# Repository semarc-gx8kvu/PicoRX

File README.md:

SEMARC Version of the PicoRX
============================

As a group we have taken Jon Dawson's design and created:

+ Our own PCB
+ The Box
+ Modifications to the Code

How we modify this fork is up to us as a group. I'm going to suggest that we have a *SEMARC* folder that contains our PCB and Box designs. But we *shouldn't* put code changes in there. I suggest that we put code changes in branches, and then decide as a group whether to include these in the main branch, or maybe even consider submitting pull requests to Jon's original repository.

Pi Pico Rx - A crystal radio for the digital age?
=================================

My first step into the world of electronics was with a crystal radio, just like this one. 

Back then, I don't think it has ever occurred to me that I could make a radio myself, so I wasn't expecting it to work. But when I put the earphone in, I was amazed to hear very faint sounds coming through. I couldn't believe that building a radio could be so simple, and the best part was, it didn't need any batteries! That little experience sparked my interest in electronics.

Times have certainly changed since then, and today, we find ourselves in a golden age for electronics enthusiasts. Back in the ninteen eightees, I could have never imagined that my pocket money would one day buy a device with computing power that could have filled an entire room just a few decades ago.

I often wonder how we can still capture that sense of awe and excitement from my first crystal radio experience. Is it still possible to create something simple yet captivating? 

The Pi Pico Rx - may be the answer to that question. While it may not be quite as straightforward as the crystal radio, the Pi Pico Rx presents a remarkably simple solution. Armed with just a [Raspberry Pi Pico](https://www.raspberrypi.com/products/raspberry-pi-pico/), an analogue switch, and an op-amp, we now have the power to construct a capable SDR receiver covering the LW, MW, and SW bands. With the ability to receive signals from halfway around the globe. I can't help but think that my younger self would have been truly impressed!

Features
--------

+ 0 - 30MHz coverage
+ 250kHz bandwidth SDR reciever
+ CW/SSB/AM/FM reception
+ OLED display
+ simple spectrum scope
+ Headphones/Speaker
+ 500 general purpose memories
+ runs on 3 AAA batteries
+ less than 50mA current consumption

Development
-----------

Pi Pico Rx is currently at the experimental prototyping stage, but it does work. [Read the Docs](https://101-things.readthedocs.io/en/latest/radio_receiver.html) for more technical details!

Getting the Code
----------------

You can find a precompiled binary for PiPicoRx [here](https://github.com/dawsonjon/PicoRX/releases). If you want to build from the C++ source files, follow these instructions.

```
  sudo apt install git
  git clone https://github.com/dawsonjon/PicoRX.git
  cd PicoRX
  git submodule init
  git submodule update
```

User Manual
-----------

You can find the user manual for the PiPicoRx [here](https://github.com/dawsonjon/PicoRX/raw/master/user_manual/Pi%20Pico%20Rx%20User%20Manual.pdf).

Install Pi Pico SDK
-------------------

Follow the [Getting started with the Raspberry Pi Pico](https://datasheets.raspberrypi.com/pico/getting-started-with-pico.pdf) quick start guide to install the C/C++ SDK.

```
  sudo apt install wget #if wget not installed
  wget https://raw.githubusercontent.com/raspberrypi/pico-setup/master/pico_setup.sh
  chmod +x pico_setup.sh
  ./pico_setup.sh
```

For windows users, this page provides and [installer](https://www.raspberrypi.com/news/raspberry-pi-pico-windows-installer/) that makes the process much simpler.

Build Projects
--------------

```
  mkdir build
  cd build
  cmake -DPICO_BOARD=pico -DPICO_SDK_PATH=~/pico/pico-sdk ..
  make
```

```
  mkdir build
  cd build
  cmake -DPICO_SDK_PATH=~/pico/pico-sdk -DPICO_BOARD=pico2 -DPICO_PLATFORM=rp2350-arm-s ..
  make
```

```
  mkdir build
  cd build
  cmake -DPICO_SDK_PATH=~/pico/pico-sdk -DPICO_BOARD=pico2 -DPICO_PLATFORM=rp2350-riscv ..
  make
```

Credits
-------

Massive thanks to everybody who has contributed and given feedback on this project. Thanks to
all your efforts, we’re closer than ever to making radio more accessible,
innovative, and community-driven.

The project uses the Universal 8-bit Graphics Library (u8g2) library by
olikraus@gmail.com, the pico_ssd1306 display library by David Schramm and the
ILI934X display driver by Darren Horrocks.

Special Thanks to:

Mariusz Ryndzionek for contributing IQ Imbalance Correction, De-emphasis
filter, USB audio, U8G2 integration, Synronous AM Demodulation and many other
enhancements.

Penfold42 for Gain Calibration, Frequency Scanning, Spectrum Zoom, Multiple home screen
views, Animated Splash Screen, Support for multiple displays/configurations and
many other enhancements.

Robert Nickels (W9RAN) and Jim Reagan (W0CHL) for their support and
encouragements and for the enormous effort they have both put in testing,
debugging, feedback and suggestions.

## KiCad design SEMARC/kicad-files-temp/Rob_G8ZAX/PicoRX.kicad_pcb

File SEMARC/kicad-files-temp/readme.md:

# How I added these files

From my laptop, I opened a powershell terminal and typed in the following commands:

```powershell
git clone git@github.com:semarc-gx8kvu/PicoRX.git
cd .\PicoRX\
git branch m0twm-add-kicad-files
git checkout m0twm-add-kicad-files
```

I then added the files in file explorer

Back in powershell, I executed the following commands:

```powershell
git add *
git commit -m 'Add schematics and pcb layouts'
git push --set-upstream origin m0twm-add-kicad-files
```

On the github website, the new branch automatically shows up and prompts you to submit a **pull request**:

On the next page, you get to name the pull request and set a description. Because this is a forked repository, you have to set the repository to the SEMARC one, because by default it will send a pull request to the base repository (jondawson) and you probbaly don't want that!

Admins get notified, and should approve the pull request as soon as possible. This is the standard approach and ensures that there are no conflicts. The files are now available on the main branch (which in this case is called master).

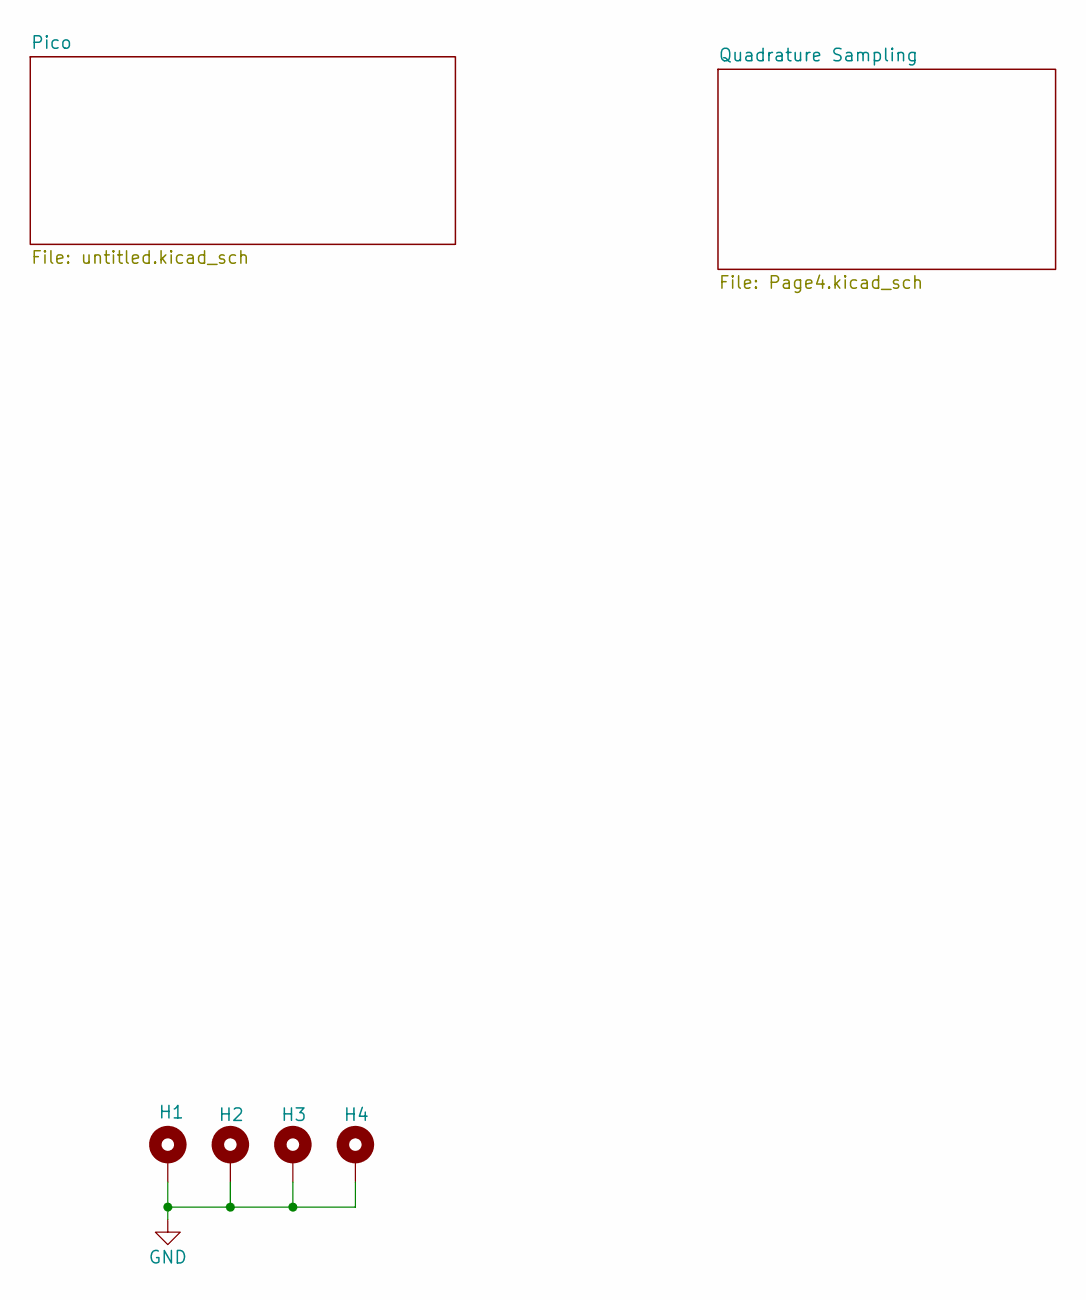
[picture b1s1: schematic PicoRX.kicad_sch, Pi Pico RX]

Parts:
H1, H2, H3, H4: MountingHole_Pad; MountingHole_3.2mm_M3_DIN965_Pad_TopBottom

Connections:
GND: H1.1, H2.1, H3.1, H4.1; also elsewhere on the board

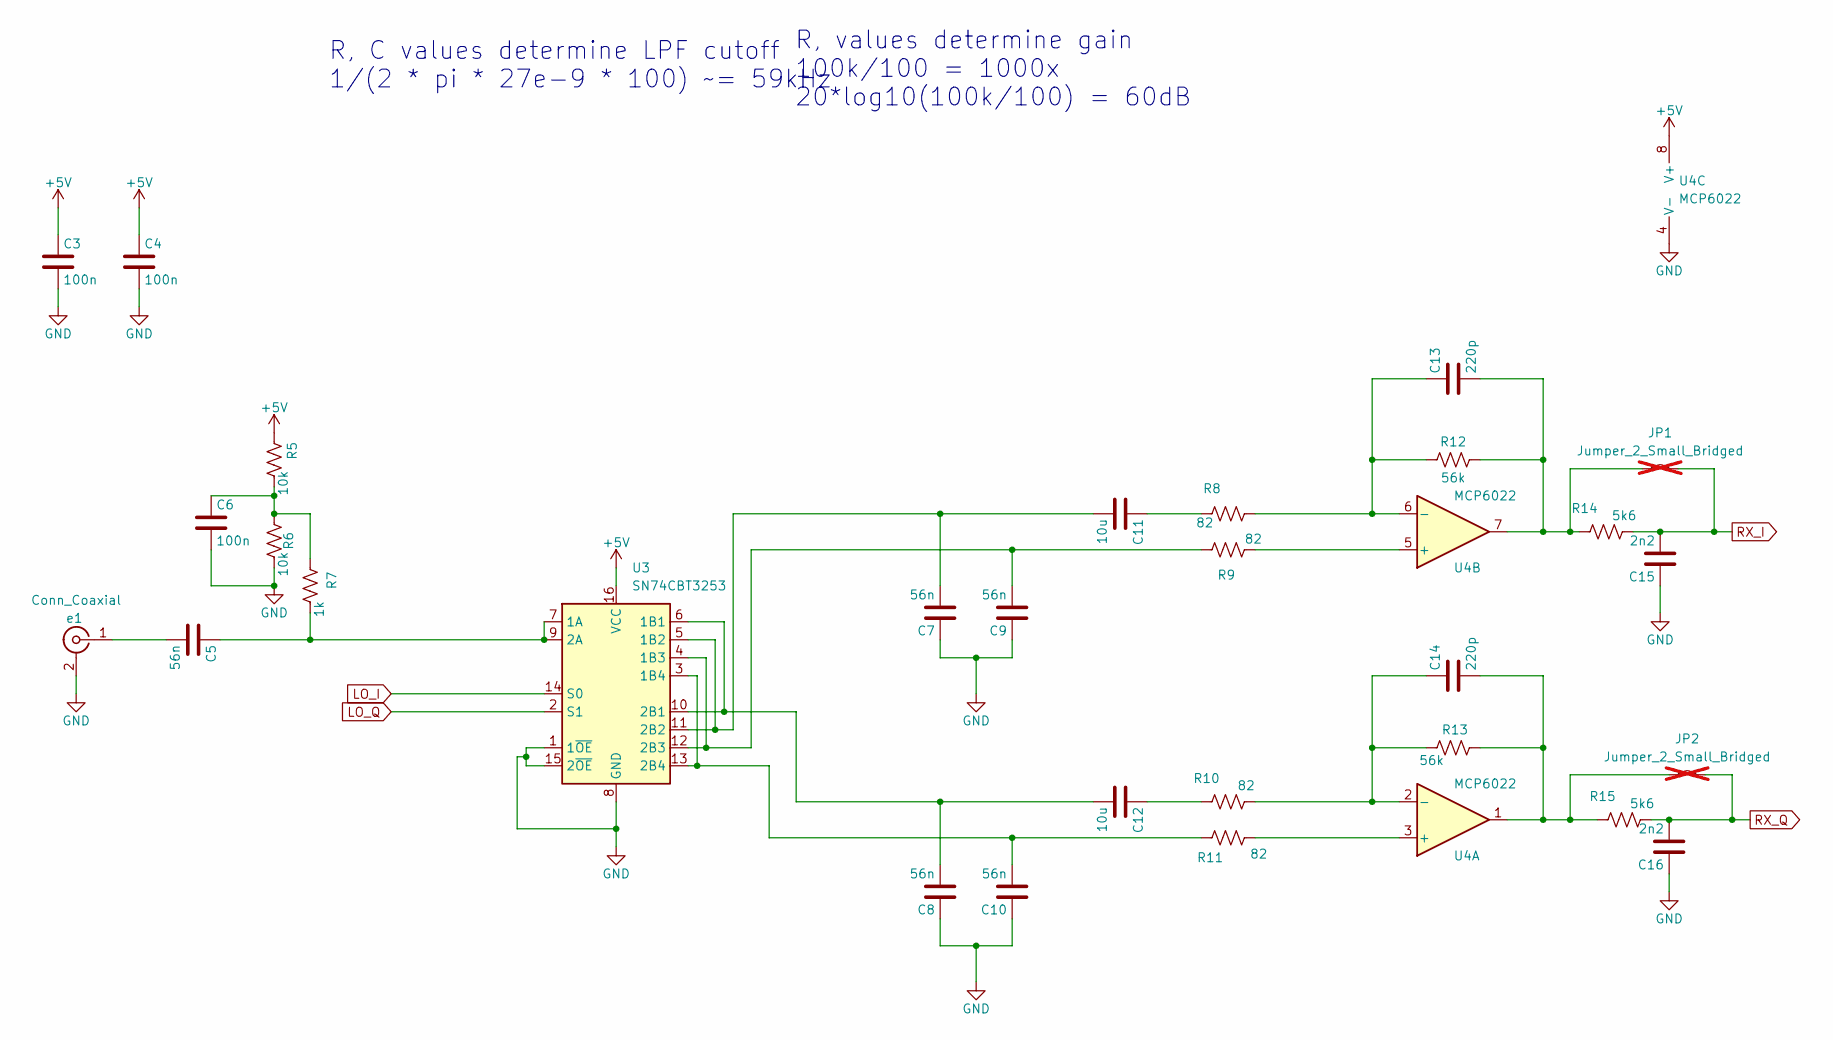
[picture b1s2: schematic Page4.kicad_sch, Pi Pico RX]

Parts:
C3, C4, C6: 100n; C_UNIV_THT2p54_SMD1206
C5, C7, C8, C9, C10: 56n; C_UNIV_THT2p54_SMD1206
C11, C12: 10u; C_UNIV_THT2p54_SMD1206
C13, C14: 220p; C_UNIV_THT2p54_SMD1206
C15, C16: 2n2; C_UNIV_THT2p54_SMD1206
JP1, JP2: Jumper_2_Small_Bridged; Jumper_P2.54mm_D0.7mm; not fitted
R5, R6: 10k; R_UNIV_AXIAL10p16_SMD1206
R7: 1k; R_UNIV_AXIAL10p16_SMD1206
R8, R9, R10, R11: 82; R_UNIV_AXIAL10p16_SMD1206
R12, R13: 56k; R_UNIV_AXIAL10p16_SMD1206
R14, R15: 5k6; R_UNIV_AXIAL10p16_SMD1206
U3: SN74CBT3253; SOIC-16_3.9x9.9mm_P1.27mm
U4: MCP6022; DIP-8_W7.62mm_LongPads
e1: Conn_Coaxial; SMA_Amphenol_901-144_Vertical

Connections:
+5V: C3.1, C4.1, R5.2, U3.16 (VCC), U4.8 (V+); also elsewhere on the board
GND: C3.2, C4.2, C6.2, C7.1, C8.1, C9.1, C10.1, C15.1, C16.1, R6.1, U3.1 (1~OE), U3.8 (GND), U3.15 (2~OE), U4.4 (V-), e1.2 (Ext); also elsewhere on the board
LO_I: U3.14 (S0); also elsewhere on the board
LO_Q: U3.2 (S1); also elsewhere on the board
unnamed: C6.1, R5.1, R6.2, R7.2
unnamed: C11.1, R8.1
unnamed: C12.1, R10.1
unnamed: C13.2, JP1.1 (A), R12.2, R14.1, U4.7
unnamed: C14.2, JP2.1 (A), R13.2, R15.1, U4.1
unnamed: C5.1, R7.1, U3.7 (1A), U3.9 (2A)
unnamed: C8.2, C12.2, U3.6 (1B1), U3.10 (2B1)
unnamed: C7.2, C11.2, U3.5 (1B2), U3.11 (2B2)
unnamed: C9.2, R9.1, U3.4 (1B3), U3.12 (2B3)
unnamed: C10.2, R11.1, U3.3 (1B4), U3.13 (2B4)
unnamed: R11.2, U4.3 (+)
unnamed: C14.1, R10.2, R13.1, U4.2 (-)
unnamed: R9.2, U4.5 (+)
unnamed: C13.1, R8.2, R12.1, U4.6 (-)
unnamed: C5.2, e1.1 (In)
RX_I: C15.2, JP1.2 (B), R14.2; also elsewhere on the board
RX_Q: C16.2, JP2.2 (B), R15.2; also elsewhere on the board

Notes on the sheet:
R, values determine gain 100k/100 = 1000x 20*log10(100k/100) = 60dB
R, C values determine LPF cutoff 1/(2 * pi * 27e-9 * 100) ~= 59kHz

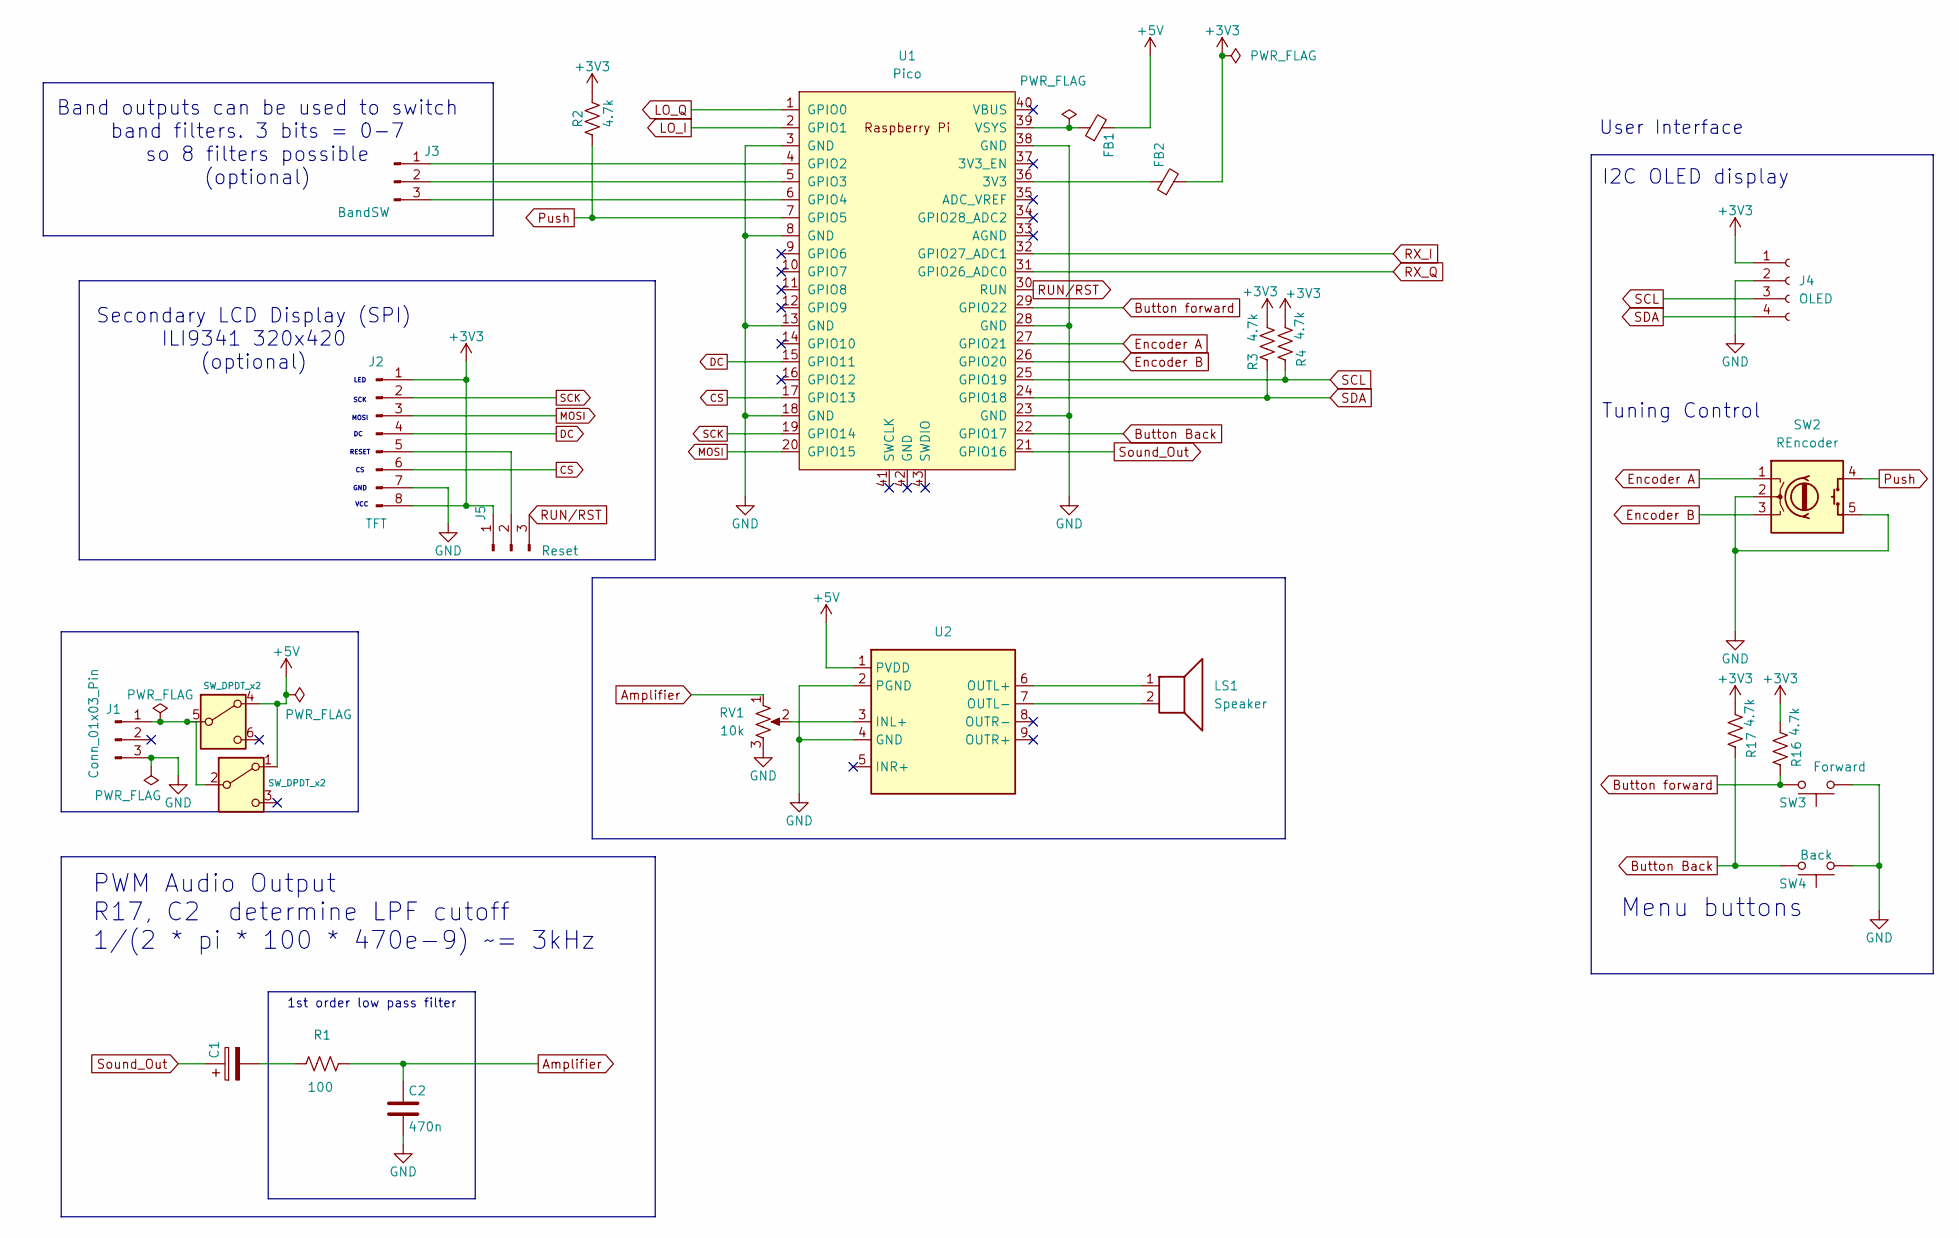
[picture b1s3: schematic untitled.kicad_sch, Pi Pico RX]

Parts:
C1: 100u; CP_Radial_D8.0mm_P2.50mm
C2: 470n; C_UNIV_THT2p54_SMD1206
FB1, FB2: FerriteBead_Small; R_Axial_DIN0207_L6.3mm_D2.5mm_P10.16mm_Horizontal
J1: Conn_01x03_Pin; PinHeader_1x03_P2.54mm_Vertical
J2: TFT; PinHeader_1x08_P2.54mm_Vertical
J3: BandSW; PinHeader_1x03_P2.54mm_Vertical
J4: OLED; PinHeader_1x04_P2.54mm_Vertical
J5: Reset; PinHeader_1x03_P2.54mm_Vertical
LS1: Speaker; PinHeader_1x02_P2.54mm_Vertical
R1: 100; R_UNIV_AXIAL10p16_SMD1206
R2, R3, R4, R16, R17: 4.7k; R_UNIV_AXIAL10p16_SMD1206
RV1: 10k; PinHeader_1x03_P2.54mm_Vertical
SW1: SW_DPDT_x2; SW_CK_JS202011CQN_DPDT_Straight
SW2: REncoder; PinHeader_1x05_P2.54mm_Vertical
SW3: Forward; PinHeader_1x02_P2.54mm_Vertical
SW4: Back; PinHeader_1x02_P2.54mm_Vertical
U1: Pico; RPi_Pico_SMD_TH
U2: Amplifier; rrAmpModule_32.3x26.5_photo_style

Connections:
+3V3: FB2.2, J2.1, J2.8, J4.1, J5.1, R2.1, R3.1, R4.1, R16.1, R17.1
+5V: FB1.2, SW1.1 (A), SW1.4 (A), U2.1 (PVDD); also elsewhere on the board
Amplifier: C2.1, R1.2, RV1.1
Button Back: R17.2, SW4.2, U1.22 (GPIO17)
Button forward: R16.2, SW3.2, U1.29 (GPIO22)
CS: J2.6, U1.17 (GPIO13)
DC: J2.4, U1.15 (GPIO11)
Encoder A: SW2.1 (A), U1.27 (GPIO21)
Encoder B: SW2.3 (B), U1.26 (GPIO20)
GND: C2.2, J1.3, J2.7, J4.2, RV1.3, SW2.2 (C), SW2.5 (S2), SW3.1, SW4.1, U1.3 (GND), U1.8 (GND), U1.13 (GND), U1.18 (GND), U1.23 (GND), U1.28 (GND), U1.38 (GND), U2.2 (PGND), U2.4 (GND); also elsewhere on the board
LO_I: U1.2 (GPIO1); also elsewhere on the board
LO_Q: U1.1 (GPIO0); also elsewhere on the board
MOSI: J2.3, U1.20 (GPIO15)
unnamed: C1.2, R1.1
unnamed: J1.1, SW1.2 (B), SW1.5 (B)
unnamed: J2.5, J5.2
unnamed: J3.1, U1.4 (GPIO2)
unnamed: J3.2, U1.5 (GPIO3)
unnamed: J3.3, U1.6 (GPIO4)
unnamed: FB2.1, U1.36 (3V3)
unnamed: FB1.1, U1.39 (VSYS)
unnamed: RV1.2, U2.3 (INL+)
unnamed: LS1.1, U2.6 (OUTL+)
unnamed: LS1.2, U2.7 (OUTL-)
Push: R2.2, SW2.4 (S1), U1.7 (GPIO5)
RUN/RST: J5.3, U1.30 (RUN)
RX_I: U1.32 (GPIO27_ADC1); also elsewhere on the board
RX_Q: U1.31 (GPIO26_ADC0); also elsewhere on the board
SCK: J2.2, U1.19 (GPIO14)
SCL: J4.3, R4.2, U1.25 (GPIO19)
SDA: J4.4, R3.2, U1.24 (GPIO18)
Sound_Out: C1.1, U1.21 (GPIO16)

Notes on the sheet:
1st order low pass filter
MOSI
Band outputs can be used to switch band filters. 3 bits = 0-7 so 8 filters possible (optional)
VCC
PWM Audio Output R17, C2 determine LPF cutoff 1/(2 * pi * 100 * 470e-9) ~= 3kHz
Tuning Control
GND
Menu buttons
LED
User Interface
RESET
SCK
Secondary LCD Display (SPI) ILI9341 320x420 (optional)
I2C OLED display

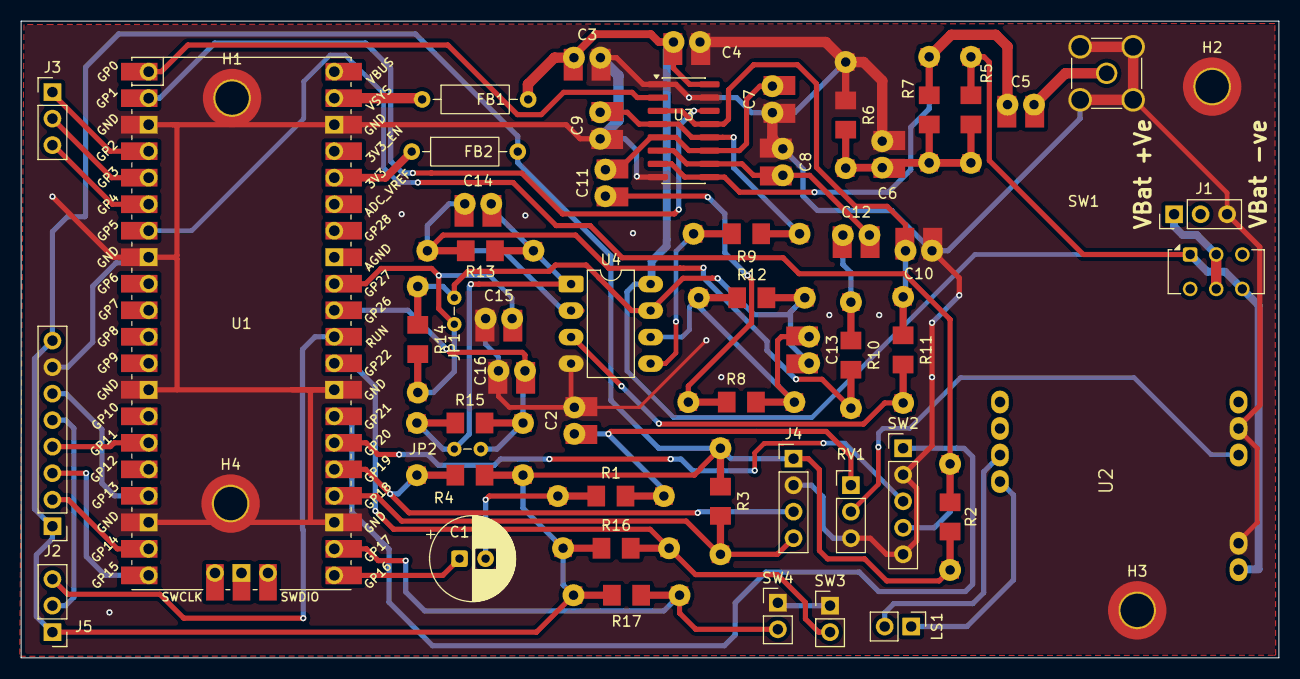
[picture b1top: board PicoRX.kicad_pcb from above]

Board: 2 copper layers, 120.5 x 61.0 mm, 57 parts (0 on the bottom side), 47 nets.
